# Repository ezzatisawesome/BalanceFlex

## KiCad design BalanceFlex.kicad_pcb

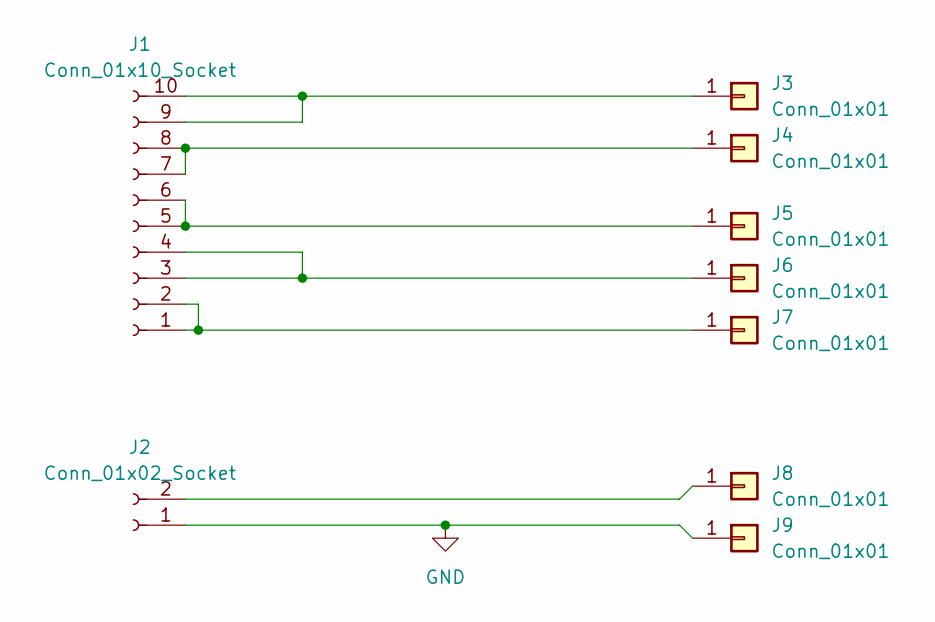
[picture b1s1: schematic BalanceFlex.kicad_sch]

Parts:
J1: Conn_01x10_Socket; tb4_10p
J2: Conn_01x02_Socket; AMASS_XT30PW-F_1x02_P2.50mm_Horizontal
J3, J4, J5, J6, J7, J8, J9: Conn_01x01; cell_connection

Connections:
GND: J2.1, J9.1
unnamed: J1.1, J1.2, J7.1
unnamed: J1.3, J1.4, J6.1
unnamed: J1.5, J1.6, J5.1
unnamed: J1.7, J1.8, J4.1
unnamed: J1.9, J1.10, J3.1
unnamed: J2.2, J8.1

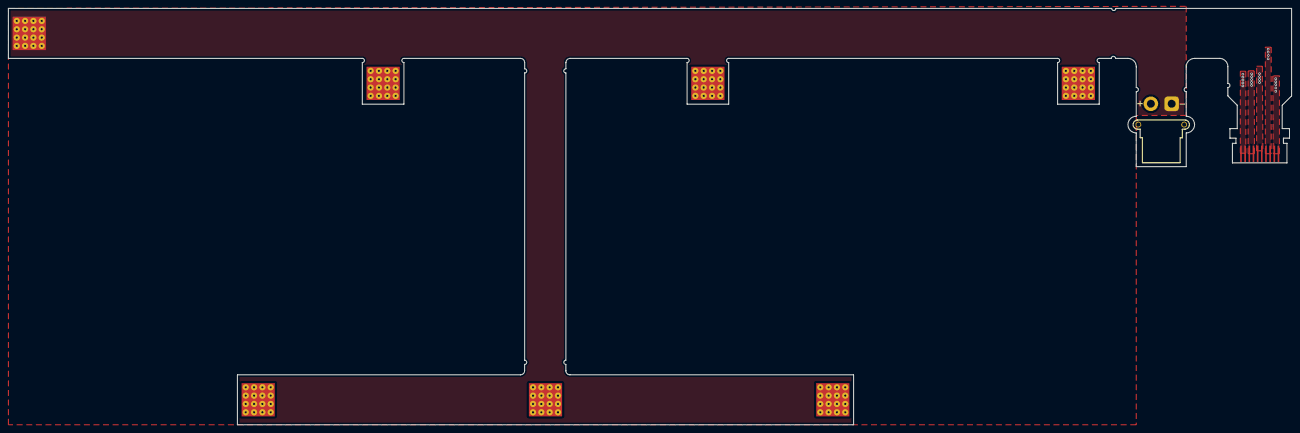
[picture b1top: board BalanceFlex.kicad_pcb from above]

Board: 4 copper layers, 308.2 x 100.0 mm, 9 parts (0 on the bottom side), 7 nets.

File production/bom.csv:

Designator,Footprint,Quantity,Value,LCSC Part #
J1,tb4_10p,1,Conn_01x10_Socket,
J2,AMASS_XT30PW-F_1x02_P2.50mm_Horizontal,1,Conn_01x02_Socket,
"J3, J4, J5, J6, J7, J8, J9",cell_connection,7,Conn_01x01,

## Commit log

2026-01-20 Cleaning up layout and adding in thermistors
2026-04-13 had to add all files because I download zip instead of cloned
2026-04-14 Tocuhing up
2026-04-17 fillet + vias
